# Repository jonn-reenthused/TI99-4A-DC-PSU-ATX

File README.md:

# TI99-4A-DC-PSU-ATX
moved to https://codeberg.org/Jonn-reenthused/TI99-4A-DC-PSU-ATX

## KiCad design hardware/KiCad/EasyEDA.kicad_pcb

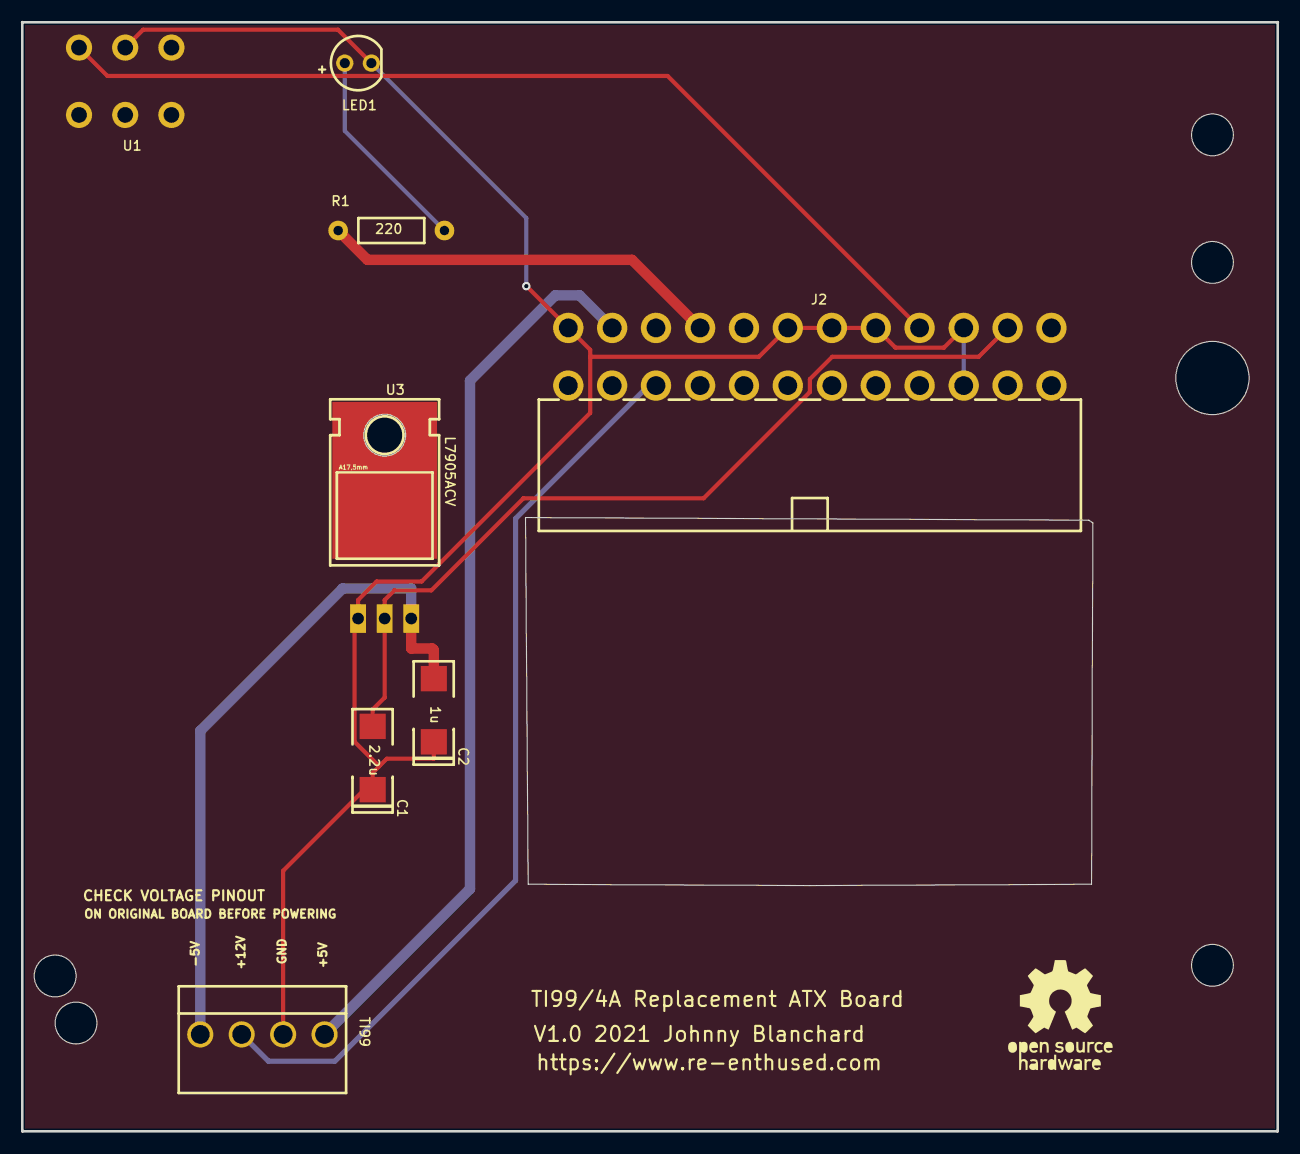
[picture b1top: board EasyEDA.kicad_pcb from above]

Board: 2 copper layers, 120.0 x 106.0 mm, 16 parts (0 on the bottom side), 8 nets.

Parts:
C1: 2.2u; CASE-C_6032
C2: 1u; CASE-C_6032
Hole_gge744: Hole_gge744
Hole_gge745: Hole_gge745
Hole_gge746: Hole_gge746
Hole_gge747: Hole_gge747
Hole_gge748: Hole_gge748
Hole_gge749: Hole_gge749
Hole_gge12811: Hole_gge12811
J2: ATX24RH; ATX24_RIGHT_ANGLE
LED1: LED-5MM; LED-5MM/2.54
Pad_gge12412: Pad_gge12412
R1: 220; L_AXIAL-0.4
TI99: Header-Male-2.54_1x4; DIP-1X4P-3.96MM-SK
U1: Slide_Switch; SLIDE_SWITCH
U3: L7905ACV; TO220

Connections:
12V: J2.10, TI99.2
+5V1: J2.23, TI99.4
+5V2: J2.21, R1.1
-5V: C2.2, TI99.1, U3.3
-12V: C1.2, J2.14, U3.2
GND: C1.1, C2.1, J2.3, J2.15, J2.17, J2.18, J2.19, J2.24, LED1.2, TI99.3, U1.2, U3.1
LED1_1: LED1.1, R1.2
PS_ON: J2.16, U1.3

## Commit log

2024-01-07 Initial commit - UNFINISHED / NOT SAFE FOR GENERAL USE
2024-10-27 added funding link
